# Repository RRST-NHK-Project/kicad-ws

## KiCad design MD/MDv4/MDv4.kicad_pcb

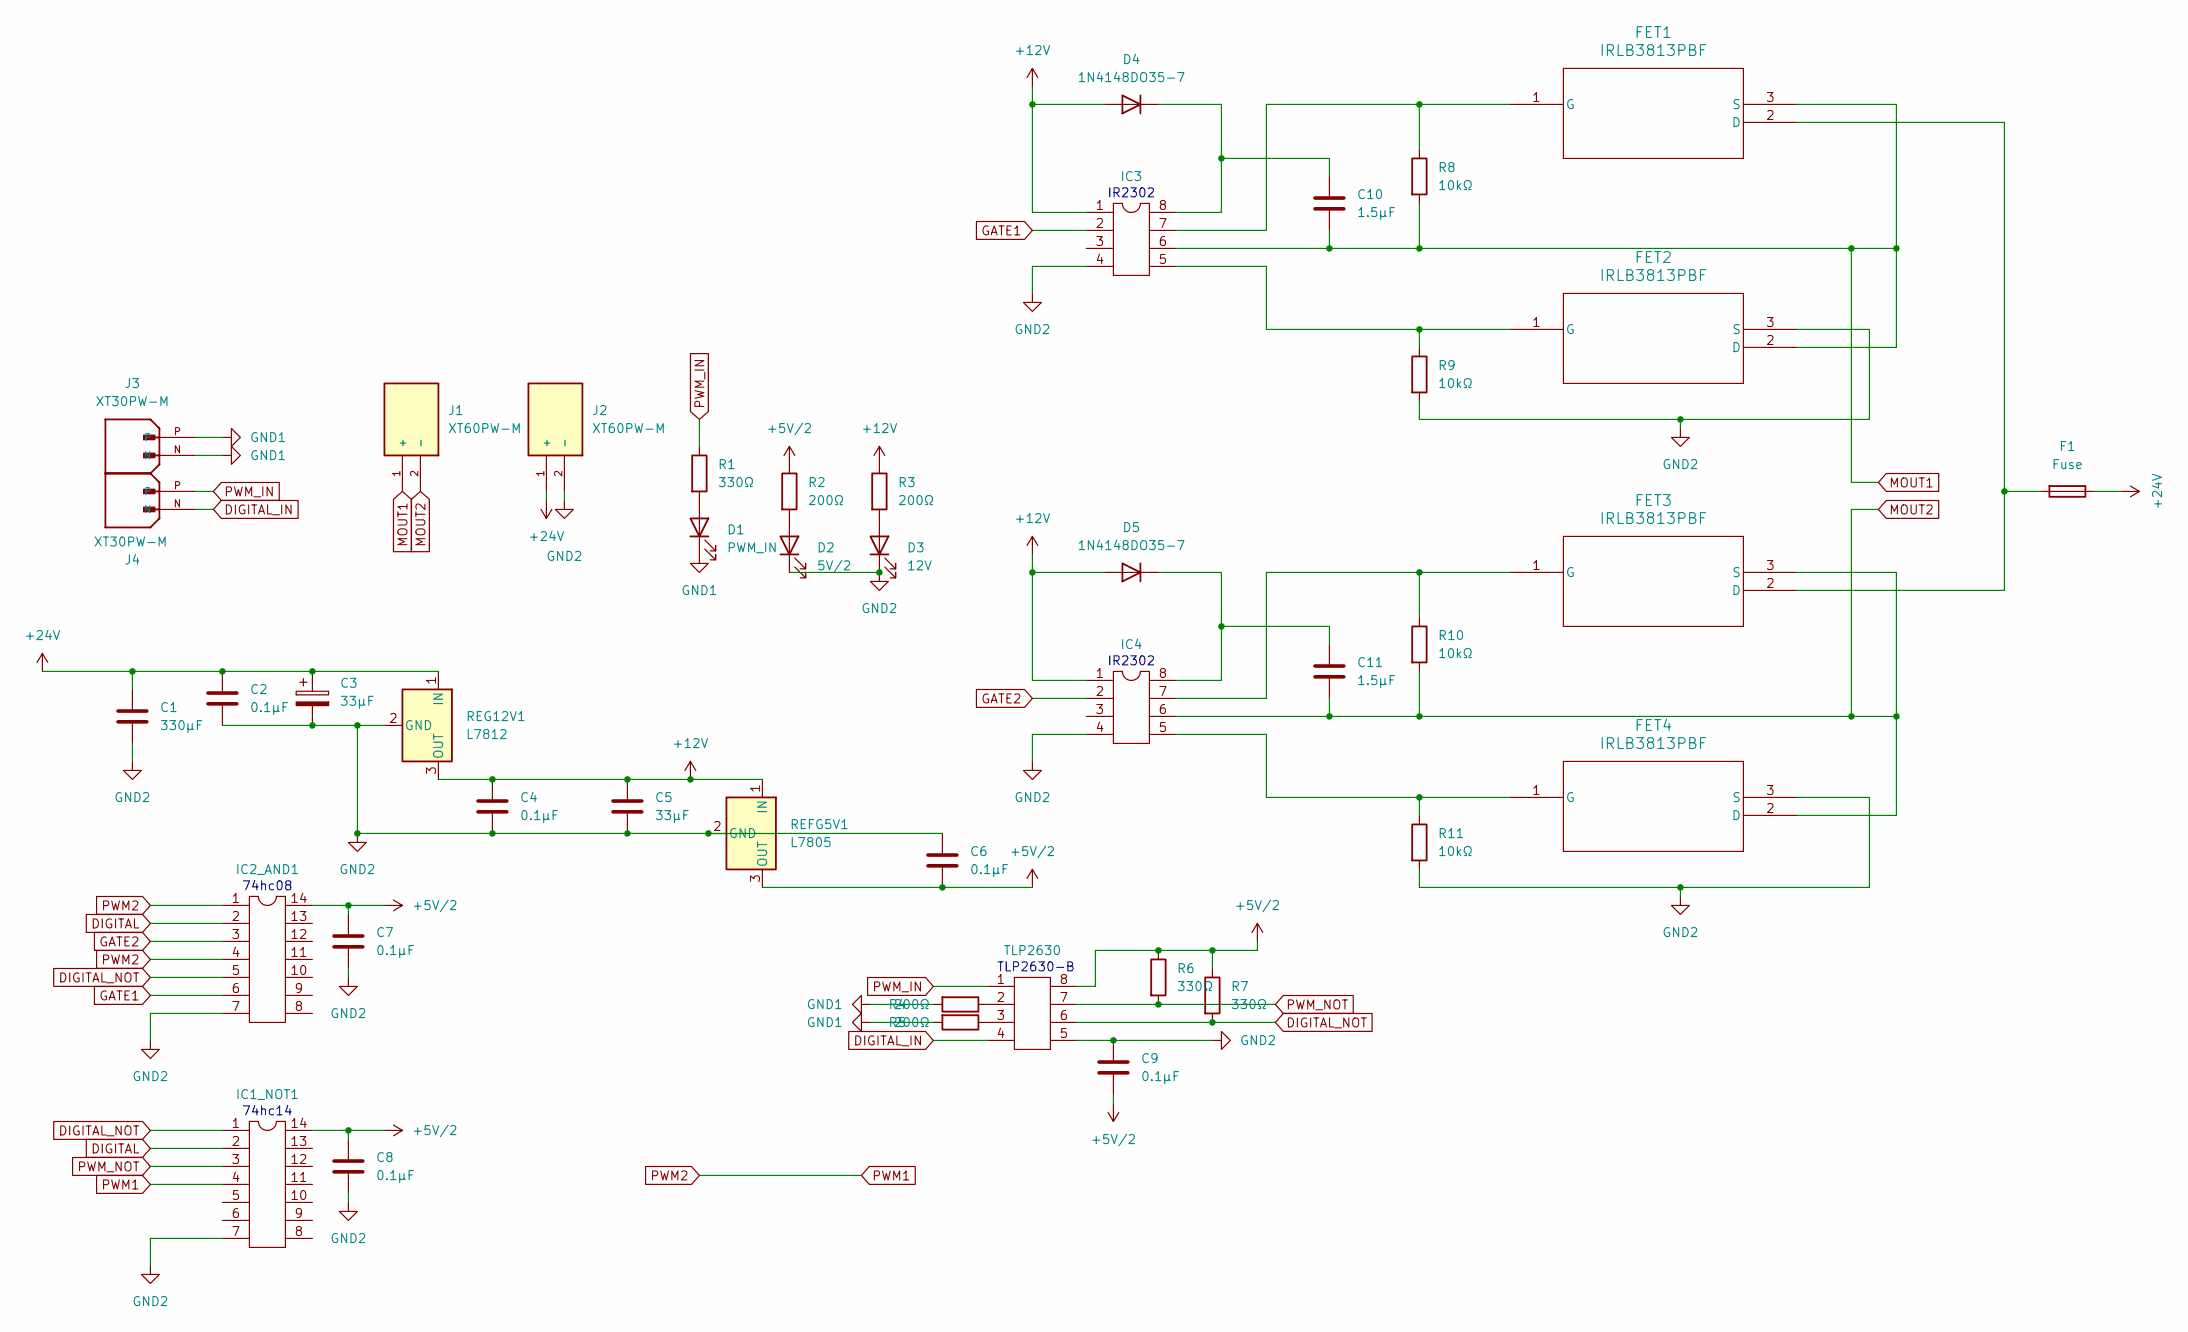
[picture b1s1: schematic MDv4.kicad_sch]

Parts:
C1: 330μF; CP_Radial_D8.0mm_P3.50mm
C2, C4, C6, C7, C8, C9: 0.1μF; C_Disc_D11.0mm_W5.0mm_P5.0mm_kai
C3, C5: 33μF; CP_Radial_D5.0mm_P2.00mm
C10, C11: 1.5μF; C_Disc_D11.0mm_W5.0mm_P5.0mm_kai
D1: PWM_IN; LED_D5.0mm
D2: 5V/2; LED_D5.0mm
D3: 12V; LED_D5.0mm
D4, D5: 1N4148DO35-7; D_DO-35_SOD27_P7.62mm_Horizontal
F1: Fuse; FUSE_3557-15
FET1, FET2, FET3, FET4: IRLB3813PBF; PG-TO220-3_INF
IC1_NOT1, IC2_AND1: DIP-14_W7.62mm
IC3, IC4: DIP-8_W7.62mm
J1, J2: XT60PW-M; AMASS_XT60PW-M; PARTREV V1.2
J3, J4: XT30PW-M; AMASS_XT30PW-M; PARTREV 1.2
R1, R6, R7: 330Ω; R_Axial_DIN0207_L6.3mm_D2.5mm_P10.16mm_Horizontal_kai
R2, R3, R4, R5: 200Ω; R_Axial_DIN0207_L6.3mm_D2.5mm_P10.16mm_Horizontal_kai
R8, R9, R10, R11: 10kΩ; R_Axial_DIN0207_L6.3mm_D2.5mm_P10.16mm_Horizontal_kai
REFG5V1: L7805; PG-TO220-3_INF
REG12V1: L7812; PG-TO220-3_INF
TLP2630: DIP-8_W7.62mm

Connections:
+5V/2: C6.2, C7.1, C8.1, C9.2, IC1_NOT1.14, IC2_AND1.14, R2.1, R6.1, R7.1, REFG5V1.3 (OUT), TLP2630.8
+12V: C4.1, C5.1, D4.2 (A), D5.2 (A), IC3.1, IC4.1, R3.1, REFG5V1.1 (IN), REG12V1.3 (OUT)
DIGITAL: IC1_NOT1.2, IC2_AND1.2
DIGITAL_IN: J4.N, TLP2630.4
DIGITAL_NOT: IC1_NOT1.1, IC2_AND1.5, R7.2, TLP2630.6
GATE1: IC2_AND1.6, IC3.2
GATE2: IC2_AND1.3, IC4.2
GND1: D1.1 (K), J3.N, J3.P, R4.2, R5.2
GND2: C1.2, C2.2, C3.2, C4.2, C5.2, C6.1, C7.2, C8.2, C9.1, D2.1 (K), D3.1 (K), FET2.3 (S), FET4.3 (S), IC1_NOT1.7, IC2_AND1.7, IC3.4, IC4.4, J2.2 (-), R9.2, R11.2, REFG5V1.2 (GND), REG12V1.2 (GND), TLP2630.5
MOUT1: C10.2, FET1.3 (S), FET2.2 (D), IC3.6, J1.1 (+), R8.2
MOUT2: C11.2, FET3.3 (S), FET4.2 (D), IC4.6, J1.2 (-), R10.2
unnamed: D1.2 (A), R1.2
unnamed: D2.2 (A), R2.2
unnamed: D3.2 (A), R3.2
unnamed: C10.1, D4.1 (K), IC3.8
unnamed: C11.1, D5.1 (K), IC4.8
unnamed: FET1.1 (G), IC3.7, R8.1
unnamed: FET2.1 (G), IC3.5, R9.1
unnamed: FET3.1 (G), IC4.7, R10.1
unnamed: FET4.1 (G), IC4.5, R11.1
unnamed: R4.1, TLP2630.2
unnamed: R5.1, TLP2630.3
PWM1: IC1_NOT1.4, IC2_AND1.1, IC2_AND1.4
PWM_IN: J4.P, R1.1, TLP2630.1
PWM_NOT: IC1_NOT1.3, R6.2, TLP2630.7

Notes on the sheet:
TLP2630-B
74hc08
IR2302
74hc14

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
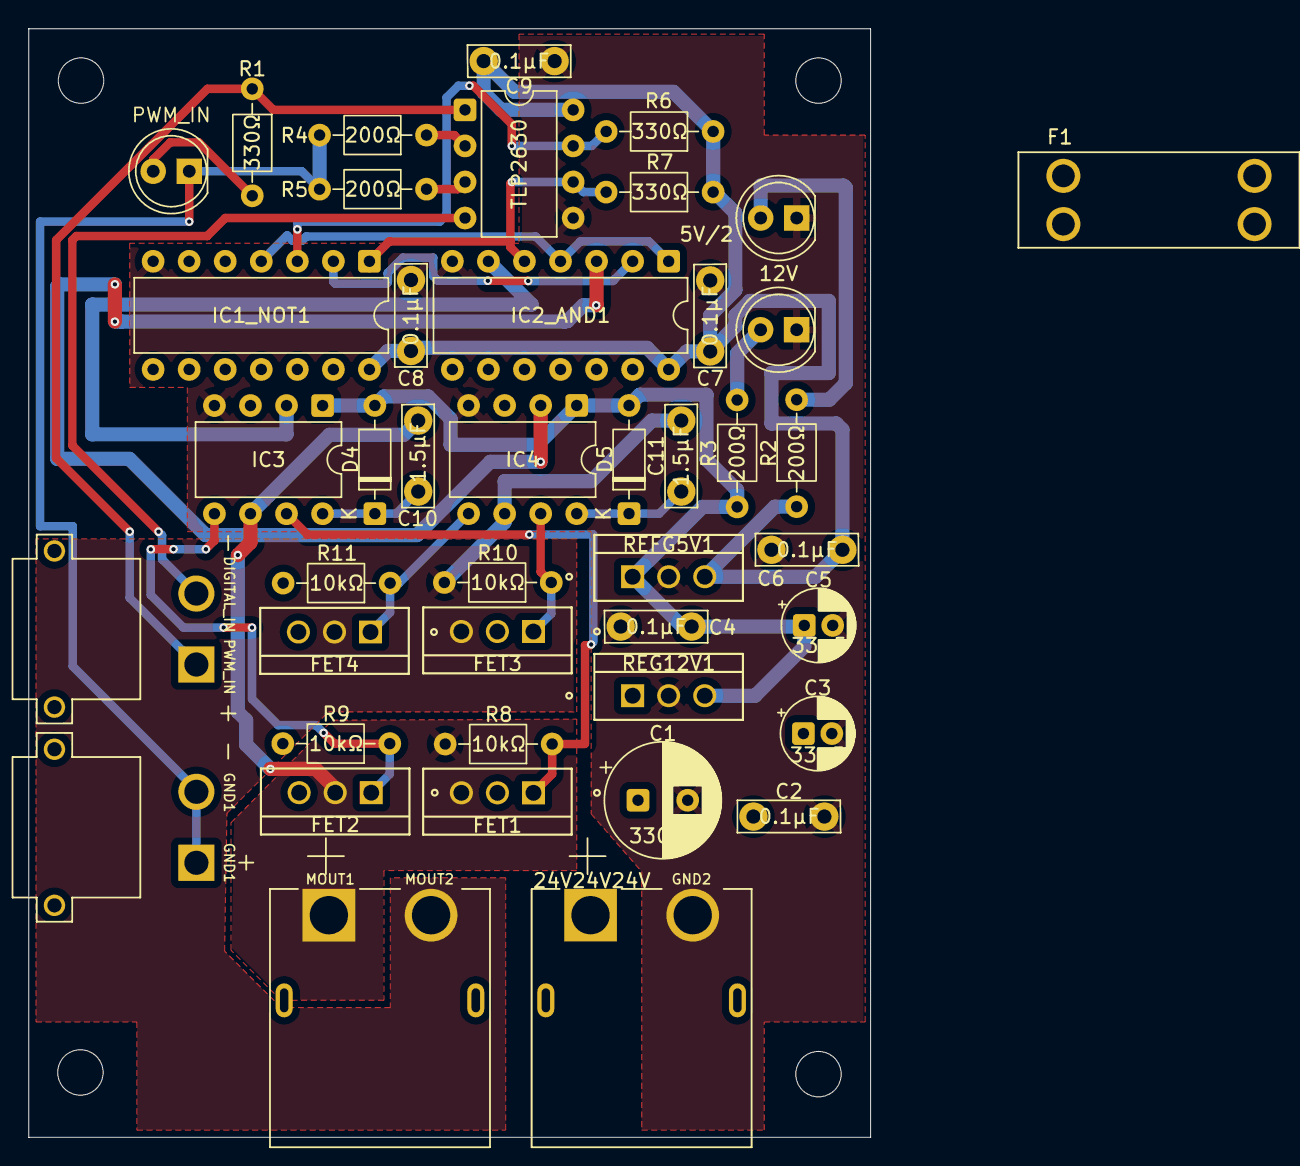
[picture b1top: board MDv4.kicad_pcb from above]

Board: 2 copper layers, 59.3 x 78.1 mm, 43 parts (0 on the bottom side), 26 nets.

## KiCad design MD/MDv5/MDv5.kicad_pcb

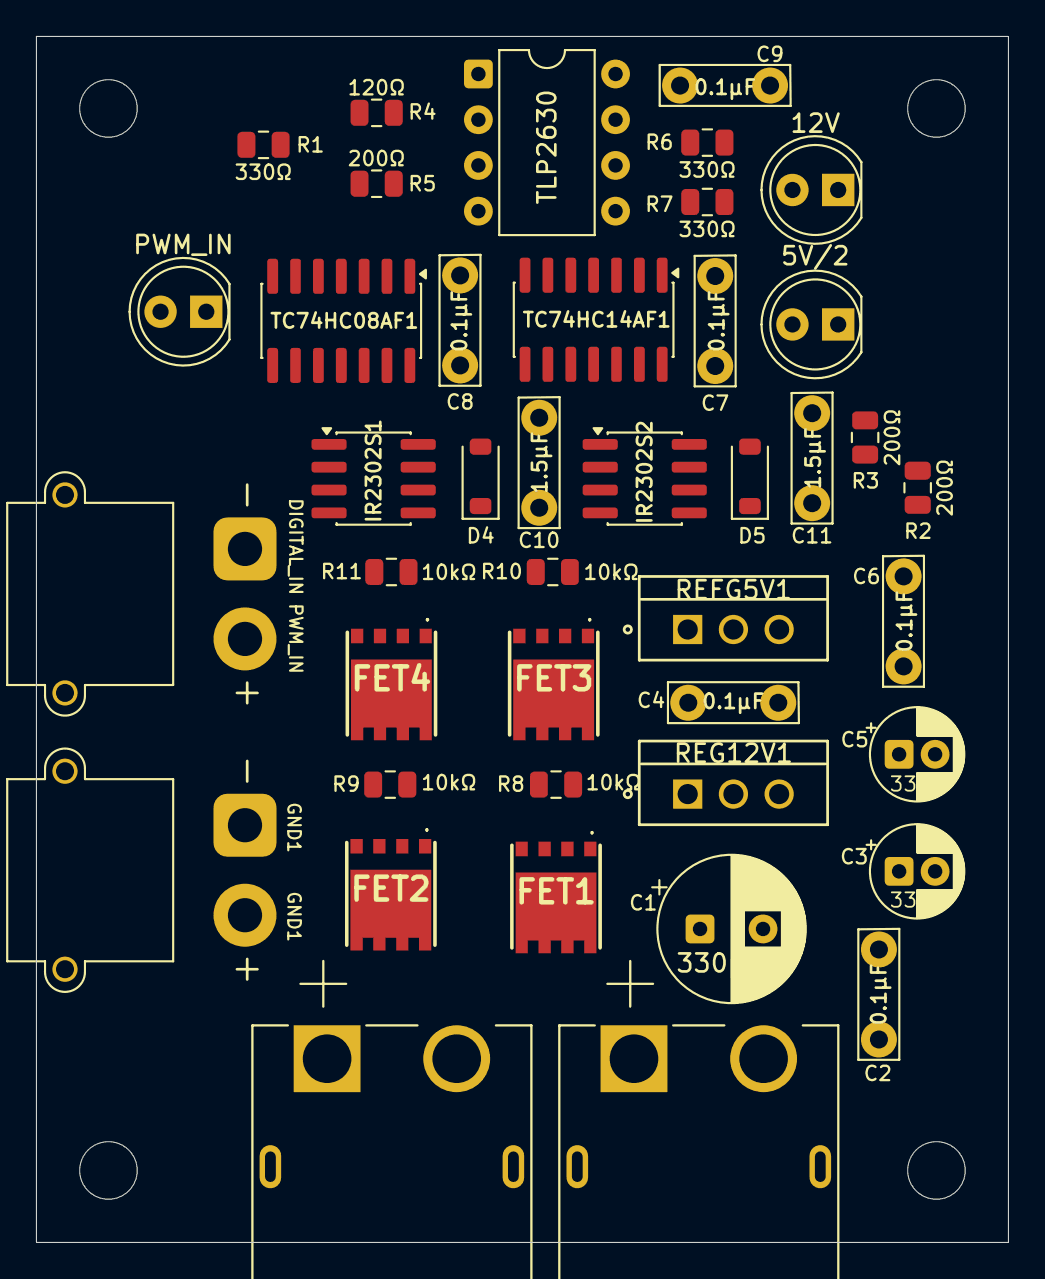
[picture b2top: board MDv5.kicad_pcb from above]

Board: 2 copper layers, 54.0 x 67.0 mm, 46 parts (0 on the bottom side), 26 nets, no tracks yet.

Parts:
C1: 330μF; CP_Radial_D8.0mm_P3.50mm
C2, C4, C6, C7, C8, C9: 0.1μF; C_Disc_D11.0mm_W5.0mm_P5.0mm_kai
C3, C5: 33μF; CP_Radial_D5.0mm_P2.00mm
C10, C11: 1.5μF; C_Disc_D11.0mm_W5.0mm_P5.0mm_kai
D1: PWM_IN; LED_D5.0mm
D2: 5V/2; LED_D5.0mm
D3: 12V; LED_D5.0mm
D4, D5: 1N4148W; D_SOD-123
FET1, FET2, FET3, FET4: RS6E120BGTB1; RS6G120BHTB1
IR2302S1, IR2302S2: SOIC-8_3.9x4.9mm_P1.27mm
J1, J2: XT60PW-M; AMASS_XT60PW-M
J3, J4: XT30PW-M; AMASS_XT30PW-M_1x02_P2.50mm_Horizontal
R1, R6, R7: 330Ω; C_0805_2012Metric
R2, R3, R5: 200Ω; C_0805_2012Metric
R4: 120Ω; C_0805_2012Metric
R8, R9, R10, R11: 10kΩ; C_0805_2012Metric
REF1, REF2, REF3, REF4: MountingHole_3.2mm_M3
REFG5V1: MC7805CDTG; PG-TO220-3_INF
REG12V1: L7812CD2T-TR; PG-TO220-3_INF
TC74HC08AF1, TC74HC14AF1: SOIC-14_3.9x8.7mm_P1.27mm
TLP2630: DIP-8_W7.62mm

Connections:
+5V/2: C6.2, C7.1, C8.1, C9.2, R2.1, R6.1, R7.1, REFG5V1.3 (OUT), TC74HC08AF1.14, TC74HC14AF1.14, TLP2630.8
+12V: C4.1, C5.1, D4.2 (A), D5.2 (A), IR2302S1.1, IR2302S2.1, R3.1, REFG5V1.1 (IN), REG12V1.3 (OUT)
+24V: C1.1, C2.1, C3.1, FET1.5 (D_1), FET1.6 (D_2), FET1.7 (D_3), FET1.8 (D_4), FET1.9 (D_5), FET3.5 (D_1), FET3.6 (D_2), FET3.7 (D_3), FET3.8 (D_4), FET3.9 (D_5), J2.P (+), REG12V1.1 (IN)
DIGITAL: TC74HC08AF1.2, TC74HC14AF1.2
DIGITAL_IN: J4.N, TLP2630.4
DIGITAL_NOT: R7.2, TC74HC08AF1.5, TC74HC14AF1.1, TLP2630.6
GATE1: IR2302S1.2, TC74HC08AF1.6
GATE2: IR2302S2.2, TC74HC08AF1.3
GND1: D1.1 (K), J3.N, J3.P, R4.2, R5.2
GND2: C1.2, C2.2, C3.2, C4.2, C5.2, C6.1, C7.2, C8.2, C9.1, D2.1 (K), D3.1 (K), FET2.1 (S_1), FET2.2 (S_2), FET2.3 (S_3), FET4.1 (S_1), FET4.2 (S_2), FET4.3 (S_3), IR2302S1.4, IR2302S2.4, J2.N (-), R9.2, R11.2, REFG5V1.2 (GND), REG12V1.2 (GND), TC74HC08AF1.7, TC74HC14AF1.7, TLP2630.5
MOUT1: C10.2, FET1.1 (S_1), FET1.2 (S_2), FET1.3 (S_3), FET2.5 (D_1), FET2.6 (D_2), FET2.7 (D_3), FET2.8 (D_4), FET2.9 (D_5), IR2302S1.6, J1.P (+), R8.2
MOUT2: C11.2, FET3.1 (S_1), FET3.2 (S_2), FET3.3 (S_3), FET4.5 (D_1), FET4.6 (D_2), FET4.7 (D_3), FET4.8 (D_4), FET4.9 (D_5), IR2302S2.6, J1.N (-), R10.2
unnamed: D1.2 (A), R1.2
unnamed: D2.2 (A), R2.2
unnamed: D3.2 (A), R3.2
unnamed: C10.1, D4.1 (K), IR2302S1.8
unnamed: C11.1, D5.1 (K), IR2302S2.8
unnamed: FET1.4 (G), IR2302S1.7, R8.1
unnamed: FET2.4 (G), IR2302S1.5, R9.1
unnamed: FET3.4 (G), IR2302S2.7, R10.1
unnamed: FET4.4 (G), IR2302S2.5, R11.1
unnamed: R4.1, TLP2630.2
unnamed: R5.1, TLP2630.3
PWM1: TC74HC08AF1.1, TC74HC08AF1.4, TC74HC14AF1.4
PWM_IN: J4.P, R1.1, TLP2630.1
PWM_NOT: R6.2, TC74HC14AF1.3, TLP2630.7
